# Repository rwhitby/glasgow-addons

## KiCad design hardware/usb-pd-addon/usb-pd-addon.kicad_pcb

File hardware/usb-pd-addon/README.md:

# Glasgow USB-PD Add-On

## Goals

- Enable Glasgow applet control of a USB-PD PHY to emulate the following functionalities:
  - Sink
  - Source
  - DRP
  - Active Cable (SOP'/SOP'')
  - Snooping (no pull-up/pull-down on CC1/CC2 and no GoodCRC responses)

- Control a 5V load switch to drive VBUS for Source operation
  - Will only drive 5V but should tolerate 20V as a sink
    - This will be achieved using an isolation jumper

- Be able to send VDMs to control debug interfaces on certain computers
  - Need to support SOP'Debug and SOP'Debug messages

- Enable UART and I2C functionality for D+/D- and SBU1/SBU2 (debug interfaces)
  - These must go down to 1.2V and up to 3.3V
  - The D+/D- and SBU1/SBU2 pairs may both be at 1.8V to 3.3V (same voltage for both)
  - Either or both D+/D- and SBU1/SBU2 pairs may be at 1.2V
  - Selection of 1.2V or (1.8V to 3.3V) is under software control

- Negotation of PD contract may need to be done in gateware
  - The timing may be too constrained to do this on the python host side

- Putting a Luna USB stack in the FPGA is out of scope
  - But we should make it easy to connect a Luna board externally for this

- Assembly at JLCPCB
  - Choosing Basic Parts whereever possible to save costs

- Able to measure VBUS on either the PD controller or the Glasgow ADC (or both)
  - Need a solder bridge to isolate ADC for RevC1 or earlier boards

- All spare glasgow I/O available on via test points
  - Able to blue-wire strong pull-up or pull-down for spare I/Os

- No connection to high speed lanes
  - But possibility to snoop LSTX/LSRX on SBU1/SBU2 for TBT3/USB4

- Initially support FUSB302/FUSB302B devices
  - Testing will use FUSB302B primarily
  - Footprint compatible with FUSB302(A), but different I2C address
  - Footprint compatible with FUSB302T, but different I2C address
  - Footprint compatible with FUSB302B(01,10,11), but different I2C address

- Potentially support large extended messages by streaming the FUSB302 FIFO through the FPGA

## Applet Requirements

- Applet should start Port A at 3.3V, and check if FUSB302 is
  available, before raising voltage to 5V.  This is to prevent the
  case that plugging in the addon the wrong way around blows up the
  level shifters.

## Current Status

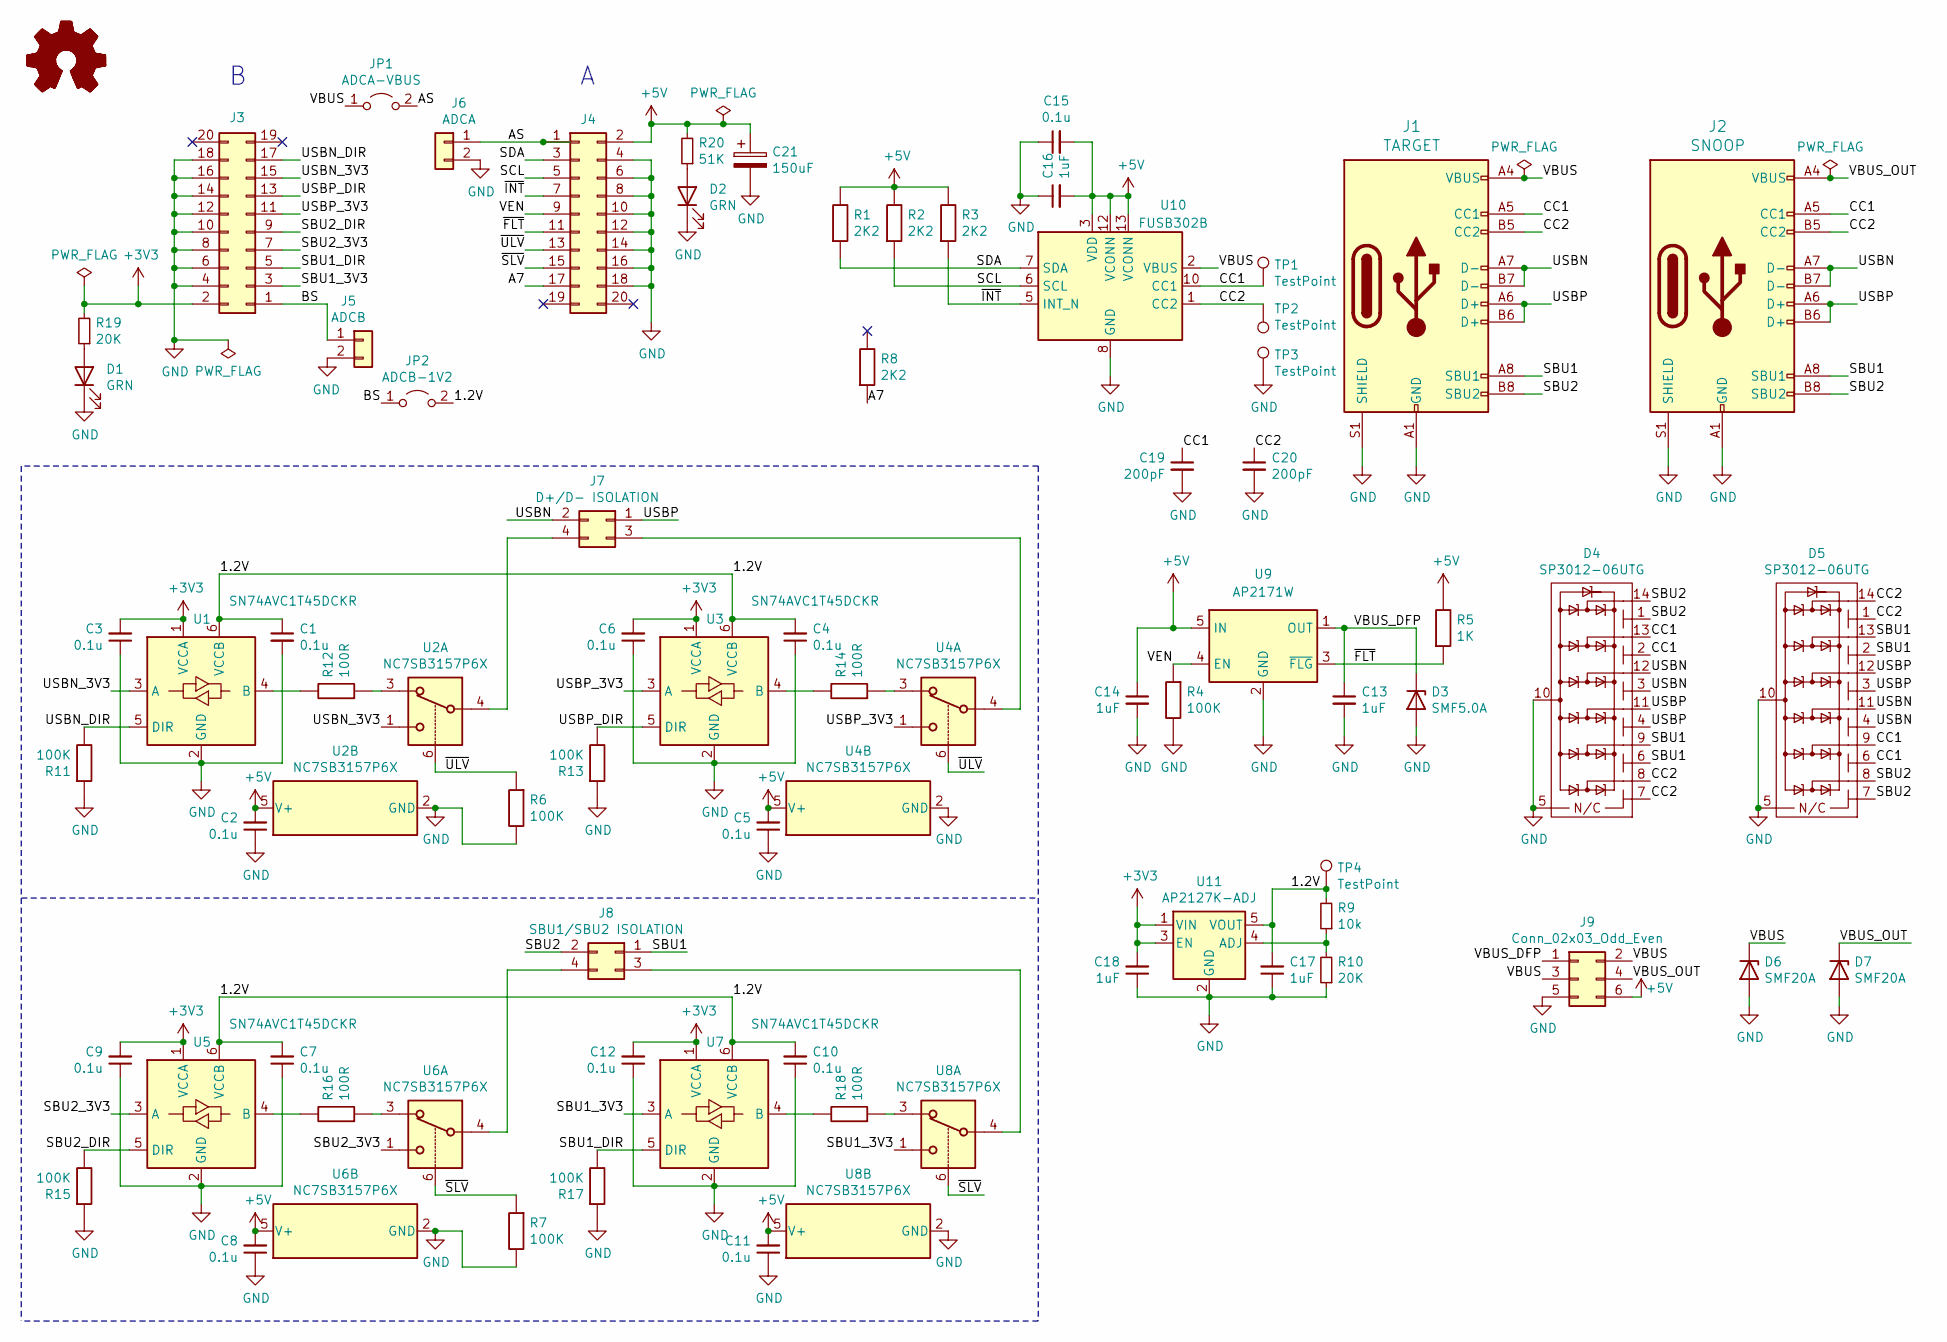
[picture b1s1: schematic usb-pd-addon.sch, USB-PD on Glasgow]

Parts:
C1, C2, C3, C4, C5, C6, C7, C8, C9, C10, C11, C12, C15: 0.1u; C_0603; LCSC C14663
C13, C14, C16, C17, C18: 1uF; C_0603; LCSC C15849
C19, C20: 200pF; C_0603; LCSC C1600
C21: 150uF; CP_Elec_6.3x7.7; LCSC C250091
D1, D2: GRN; LED_0603_1608Metric; LCSC C72043
D3: SMF5.0A; D_SOD-123F; LCSC C151296
D4, D5: SP3012-06UTG; UDFN-14_3.5x1.35mm_P0.5mm; LCSC C126838
D6, D7: SMF20A; D_SOD-123F; LCSC C151295
J1: TARGET; USB_C_Receptacle_HRO_TYPE-C-31-M-12; LCSC C165948
J2: SNOOP; USB_C_Receptacle_HRO_TYPE-C-31-M-12; LCSC C165948
J3, J4: Conn_02x10_Odd_Even; PinSocket_2x10_P2.54mm_Vertical; LCSC C50982
J5: ADCB; PinHeader_1x02_P2.54mm_Vertical; LCSC C160332
J6: ADCA; PinHeader_1x02_P2.54mm_Vertical; LCSC C160332
J7: D+/D- ISOLATION; PinHeader_2x02_P2.54mm_Vertical
J8: SBU1/SBU2 ISOLATION; PinHeader_2x02_P2.54mm_Vertical
J9: Conn_02x03_Odd_Even; PinHeader_2x03_P2.54mm_Vertical; LCSC C65114
JP1: ADCA-VBUS; SolderJumper-2_P1.3mm_Open_RoundedPad1.0x1.5mm
JP2: ADCB-1V2; SolderJumper-2_P1.3mm_Open_RoundedPad1.0x1.5mm
LOGO1, LOGO2: Logo_Open_Hardware_Small; OSHW-Logo2_7.3x6mm_SilkScreen
R1, R2, R3, R8: 2K2; R_0603; LCSC C4190
R4, R6, R7, R11, R13, R15, R17: 100K; R_0603; LCSC C25803
R5: 1K; R_0603; LCSC C21190
R9: 10k; R_0603; LCSC C25804
R10, R19: 20K; R_0603; LCSC C4184
R12, R14, R16, R18: 100R; R_0603; LCSC C22775
R20: 51K; R_0603; LCSC C23196
TP1, TP2, TP3, TP4: TestPoint; TestPoint_THTPad_1.0x1.0mm_Drill0.5mm
U1, U3, U5, U7: SN74AVC1T45DCKR; SOT-363_SC-70-6; LCSC C133077
U2, U4, U6, U8: NC7SB3157P6X; SOT-363_SC-70-6; LCSC C87403
U9: AP2171W; SOT-23-5; LCSC C110466
U10: FUSB302B; WQFN-14-1EP_2.5x2.5mm_P0.5mm_EP1.45x1.45mm; LCSC C132291
U11: AP2127K-ADJ; SOT-23-5; LCSC C96343

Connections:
+3V3: C3.2, C6.2, C9.2, C12.2, C18.2, J3.2, R19.2, U1.1 (VCCA), U3.1 (VCCA), U5.1 (VCCA), U7.1 (VCCA), U11.1 (VIN), U11.3 (EN)
+5V: C2.2, C5.2, C8.2, C11.2, C14.1, C15.2, C16.2, C21.1, J4.2, J9.6, R1.1, R2.1, R3.1, R5.1, R20.2, U2.5 (V+), U4.5 (V+), U6.5 (V+), U8.5 (V+), U9.5 (IN), U10.3 (VDD), U10.4 (VDD), U10.12 (VCONN), U10.13 (VCONN)
/1.2V: C1.1, C4.2, C7.2, C10.2, C17.2, JP2.2 (B), R9.2, TP4.1, U1.6 (VCCB), U3.6 (VCCB), U5.6 (VCCB), U7.6 (VCCB), U11.5 (VOUT)
/A7: J4.17, R8.2
/AS: J4.1, J6.1, JP1.2 (B)
/BS: J3.1, J5.1, JP2.1 (A)
/CC1: C19.1, D4.2 (N/C), D4.13 (Ch2), D5.6 (N/C), D5.9 (Ch5), J1.A5 (CC1), J2.A5 (CC1), TP1.1, U10.10 (CC1), U10.11 (CC1)
/CC2: C20.1, D4.7 (N/C), D4.8 (Ch6), D5.1 (N/C), D5.14 (Ch1), J1.B5 (CC2), J2.B5 (CC2), TP2.1, U10.1 (CC2), U10.14 (CC2)
/SBU1: D4.6 (N/C), D4.9 (Ch5), D5.2 (N/C), D5.13 (Ch2), J1.A8 (SBU1), J2.A8 (SBU1), J8.1
/SBU1_3V3: J3.3, U7.3 (A), U8.1
/SBU1_DIR: J3.5, R17.1, U7.5 (DIR)
/SBU2: D4.1 (N/C), D4.14 (Ch1), D5.7 (N/C), D5.8 (Ch6), J1.B8 (SBU2), J2.B8 (SBU2), J8.2
/SBU2_3V3: J3.7, U5.3 (A), U6.1
/SBU2_DIR: J3.9, R15.1, U5.5 (DIR)
/SCL: J4.5, R2.2, U10.6 (SCL)
/SDA: J4.3, R1.2, U10.7 (SDA)
/USBN: D4.3 (N/C), D4.12 (Ch3), D5.4 (N/C), D5.11 (Ch4), J1.A7 (D-), J1.B7 (D-), J2.A7 (D-), J2.B7 (D-), J7.2
/USBN_3V3: J3.15, U1.3 (A), U2.1
/USBN_DIR: J3.17, R11.1, U1.5 (DIR)
/USBP: D4.4 (N/C), D4.11 (Ch4), D5.3 (N/C), D5.12 (Ch3), J1.A6 (D+), J1.B6 (D+), J2.A6 (D+), J2.B6 (D+), J7.1
/USBP_3V3: J3.11, U3.3 (A), U4.1
/USBP_DIR: J3.13, R13.1, U3.5 (DIR)
/VBUS: D6.1 (K), J1.A4 (VBUS), J1.A9 (VBUS), J1.B4 (VBUS), J1.B9 (VBUS), J9.2, J9.3, JP1.1 (A), U10.2 (VBUS)
/VBUS_DFP: C13.1, D3.1 (K), J9.1, U9.1 (OUT)
/VBUS_OUT: D7.1 (K), J2.A4 (VBUS), J2.A9 (VBUS), J2.B4 (VBUS), J2.B9 (VBUS), J9.4
/VEN: J4.9, R4.2, U9.4 (EN)
/~FLT: J4.11, R5.2, U9.3 (~FLG)
/~INT: J4.7, R3.2, U10.5 (INT_N)
/~SLV: J4.15, R7.2, U6.6, U8.6
/~ULV: J4.13, R6.2, U2.6, U4.6
GND: C1.2, C2.1, C3.1, C4.1, C5.1, C6.1, C7.1, C8.1, C9.1, C10.1, C11.1, C12.1, C13.2, C14.2, C15.1, C16.1, C17.1, C18.1, C19.2, C20.2, C21.2, D1.1 (K), D2.1 (K), D3.2 (A), D4.5 (N/C), D4.10 (GND), D5.5 (N/C), D5.10 (GND), D6.2 (A), D7.2 (A), J1.A1 (GND), J1.A12 (GND), J1.B1 (GND), J1.B12 (GND), J1.S1 (SHIELD), J2.A1 (GND), J2.A12 (GND), J2.B1 (GND), J2.B12 (GND), J2.S1 (SHIELD), J3.4, J3.6, J3.8, J3.10, J3.12, J3.14, J3.16, J3.18, J4.4, J4.6, J4.8, J4.10, J4.12, J4.14, J4.16, J4.18, J5.2, J6.2, J9.5, R4.1, R6.1, R7.1, R10.1, R11.2, R13.2, R15.2, R17.2, TP3.1, U1.2 (GND), U2.2 (GND), U3.2 (GND), U4.2 (GND), U5.2 (GND), U6.2 (GND), U7.2 (GND), U8.2 (GND), U9.2 (GND), U10.8 (GND), U10.9 (GND), U10.15 (GND), U11.2 (GND)
unnamed: D1.2 (A), R19.1
unnamed: D2.2 (A), R20.1
unnamed: J7.3, U4.4
unnamed: J7.4, U2.4
unnamed: J8.3, U8.4
unnamed: J8.4, U6.4
unnamed: R9.1, R10.2, U11.4 (ADJ)
unnamed: R12.1, U1.4 (B)
unnamed: R12.2, U2.3
unnamed: R14.1, U3.4 (B)
unnamed: R14.2, U4.3
unnamed: R16.1, U5.4 (B)
unnamed: R16.2, U6.3
unnamed: R18.1, U7.4 (B)
unnamed: R18.2, U8.3

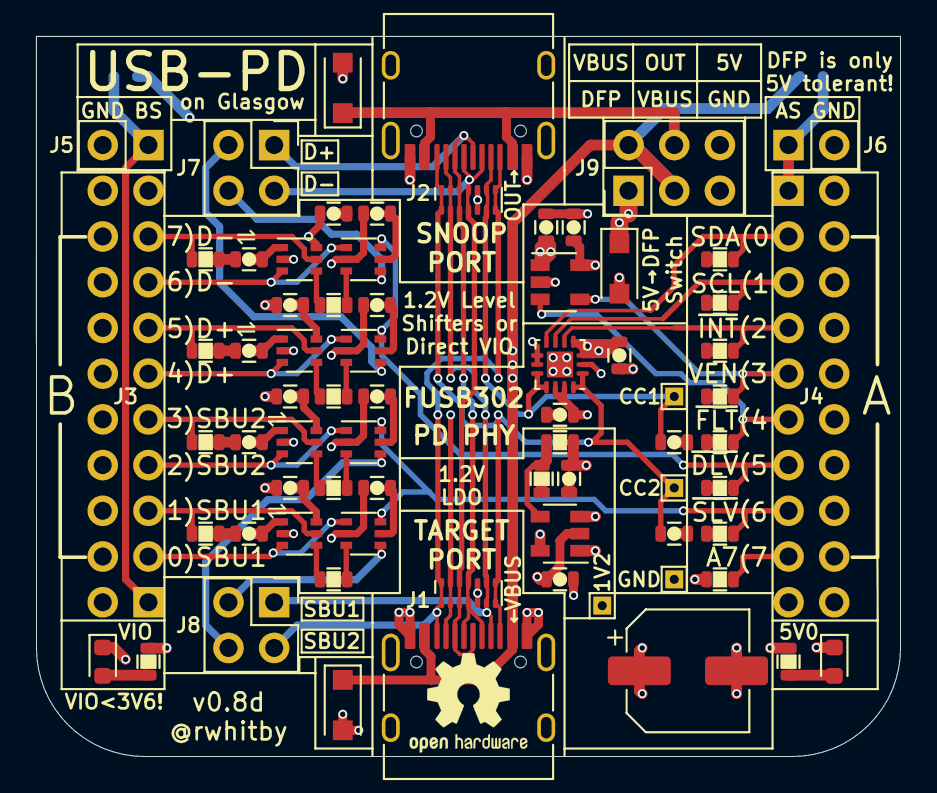
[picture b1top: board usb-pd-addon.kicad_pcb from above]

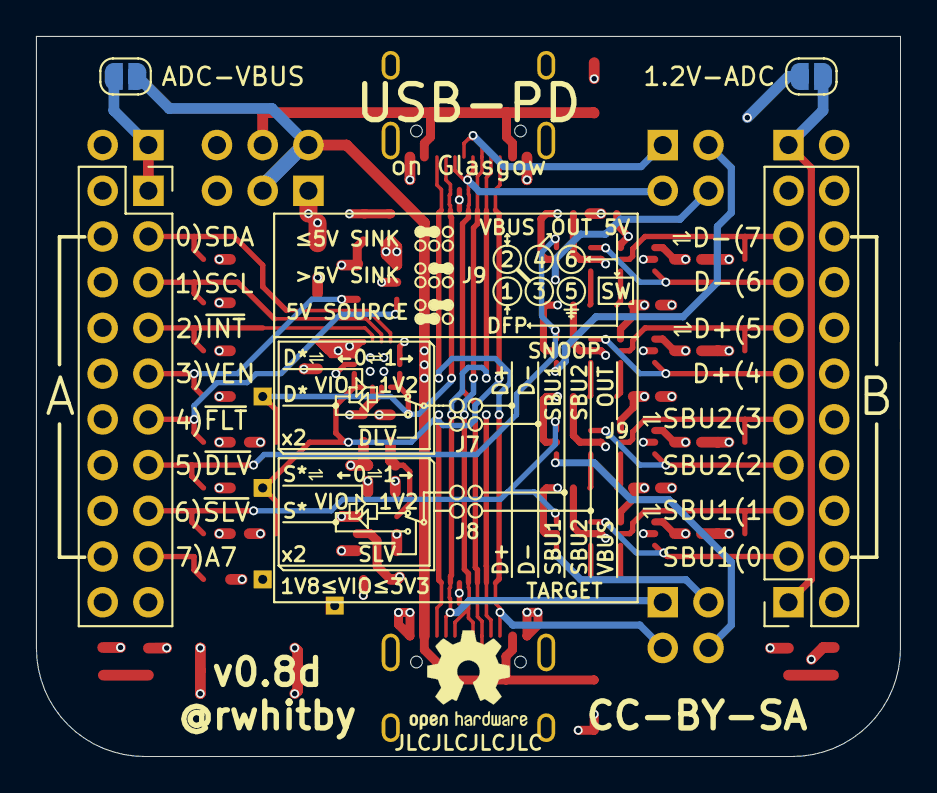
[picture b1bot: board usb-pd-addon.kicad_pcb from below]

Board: 4 copper layers, 48.0 x 40.0 mm, 76 parts (5 on the bottom side), 46 nets.

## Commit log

2021-02-07 Initial version of USB-PD add-on.
2021-02-09 v0.2a: Added adjustable LDOs for the level shifter reference voltages for USB and SBU pairs.
2021-02-09 Updated USB-C symbol, no functional change.
2021-02-11 Added more resistors to fine tune level shifter reference voltages.
2021-02-12 Added bypass caps.
2021-02-12 Corrected D+ pullup circuitry and added bypass cap.
2021-02-12 Better mnemonic for the FS pull-up switch enable.
2021-02-13 Added LEDs and a README.
2021-02-13 Changed 5V LED resistor to 51K
2021-02-14 Updated README, better silk for voltage control jumpers.
2021-02-16 Remove the D+ pullup, cause Glasgow will not support Luna USB stack. Added 2 spare SOT23 footprints.
2021-02-16 Add output files for easy viewing.
2021-02-17 Added pictures to README
2021-02-19 v0.3a: revamped the level shifting, reusing glasgow hardware for 1.8V to 3.3V
2021-02-19 v0.4a: Added decoupling for FUSB302, and protection for DFP mode operation.
2021-02-22 v0.5a: bulk capacitor for 5V supply and lots of protection added, added more silk.
2021-02-24 v0.6a: Changed to 4 layer board, added caps on CC1/CC2, squared top edge of board, increased silk legibility.
2021-02-24 Update version on schematic too.
2021-02-24 Add inner layers to PCB PDF.
2021-02-24 Updated power plane regions.
2021-02-24 Update pictures.
2021-02-25 v0.7a: analog switches instead of jumpers
2021-02-26 Interim version for review
    Changed level shifters to smaller footprint.
    Added pull-down resistors on direction signals and analog switch selects.
2021-03-01 Widened some power traces.
2021-03-01 v0.8a: Colocated D+/D- and SBU1/SBU2 jumpers. Moved ASA/ASB jumpers away from Glasgow headers.
2021-03-01 Small silk improvements
2021-03-02 v0.8b: Lots of silk improvements on front side. Relayout of center column of wires. Extended USB-C connectors past board edge.
2021-03-05 Ordered annotations and rotated components.
2021-03-07 v0.8c: Added 1.2V test point and more front silk improvements.
2021-03-14 v0.8d: Close to final rear silk documentation.
2021-03-14 Updated the README to reflect current status.

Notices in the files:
hardware/usb-pd-addon/usb-pd-addon.kicad_pcb:
License: CC-BY-SA 4.0
(C) 2020-2021 1BitSquared
(C) 2020-2021 Piotr Esden-Tempski
(C) 2021 Rod Whitby
CC-BY-SA
